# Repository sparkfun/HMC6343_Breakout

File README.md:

SparkFun HMC6343 Breakout
=========================

[*SparkFun HMC6343 Breakout (SEN-12916)*](https://www.sparkfun.com/products/12916)

A Breakout Board for the high end HMC6343 magnetometer.
The HMC6343 is a fully integrated high end electronic compass module that can compute and give you a heading direction that’s accurate within a couple degrees.

Repository Contents
-------------------
* **/Hardware** - All Eagle design files (.brd, .sch)
* **/Production** - Test bed files and production panel files

Documentation
--------------
* **[Library](https://github.com/sparkfun/SparkFun_HMC6343_Arduino_Library)** - Arduino library for the HMC6343.
* **[Hookup Guide](https://learn.sparkfun.com/tutorials/hmc6343-3-axis-compass-hookup-guide)** - Basic hookup guide for the HMC6343.
* **[SparkFun Fritzing repo](https://github.com/sparkfun/Fritzing_Parts)** - Fritzing diagrams for SparkFun products.
* **[SparkFun 3D Model repo](https://github.com/sparkfun/3D_Models)** - 3D models of SparkFun products. 
* **[SparkFun Graphical Datasheets](https://github.com/sparkfun/Graphical_Datasheets)** -Graphical Datasheets for various SparkFun products.

Version History
---------------

* [v_H1.0_L1.1.0](https://github.com/sparkfun/HMC6343_Breakout/tree/v_H1.0_L1.1.0) - Hardware version 1.0, library version 1.1.0. Compatible with Arduino 1.6+ 
* [vH10F10](https://github.com/sparkfun/HMC6343_Breakout/tree/vH10F10) - Hardware version 1.0, firmware version 1.0

License Information
-------------------

This product is _**open source**_! 

Please review the LICENSE.md file for license information. 

If you have any questions or concerns on licensing, please contact technical support on our [SparkFun forums](https://forum.sparkfun.com/viewforum.php?f=152).

Distributed as-is; no warranty is given.

- Your friends at SparkFun.

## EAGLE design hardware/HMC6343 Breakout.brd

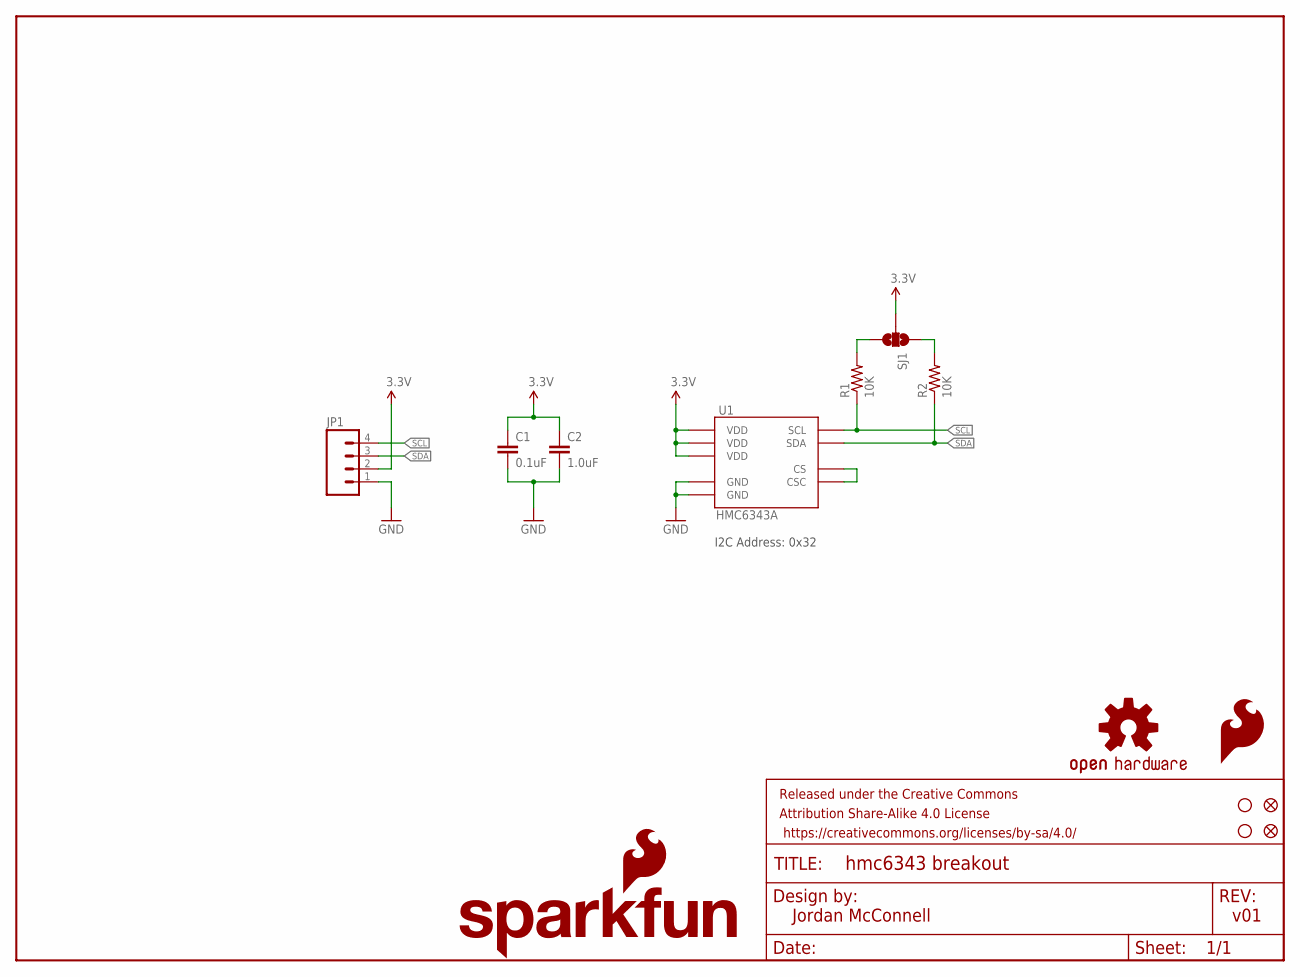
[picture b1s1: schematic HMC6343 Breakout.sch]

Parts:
C1: 0.1uF; 0603-CAP
C2: 1.0uF; 0603-CAP
FID1, FID2: FIDUCIAL1X2; FIDUCIAL-1X2
FRAME1: FRAME-LETTER; CREATIVE_COMMONS
JP1: M04PTH; 1X04
LOGO1: SFE_LOGO_FLAME.1_INCH; SFE_LOGO_FLAME_.1
LOGO2: SFE_LOGO_NAME_FLAME.1_INCH; SFE_LOGO_NAME_FLAME_.1
LOGO3: OSHW-LOGOS; OSHW-LOGO-S
R1, R2: 10K; 0603-RES
SJ1: SOLDERJUMPER_2WAYPASTE1&2&3; SJ_3_PASTE1&2&3
STANDOFF1, STANDOFF2: STAND-OFF
U1: HMC6343A; LCC36

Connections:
3.3V: C1.1, C2.1, JP1.2, SJ1.2, U1.3 (VDD), U1.11 (VDD), U1.21 (VDD)
GND: C1.2, C2.2, JP1.1, U1.25 (GND), U1.29 (GND)
unnamed: U1.22 (CS), U1.35 (CSC)
unnamed: R1.2, SJ1.3
unnamed: R2.2, SJ1.1
SCL: JP1.4, R1.1, U1.32 (SCL)
SDA: JP1.3, R2.1, U1.36 (SDA)

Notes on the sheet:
Jordan McConnell
v01
I2C Address: 0x32

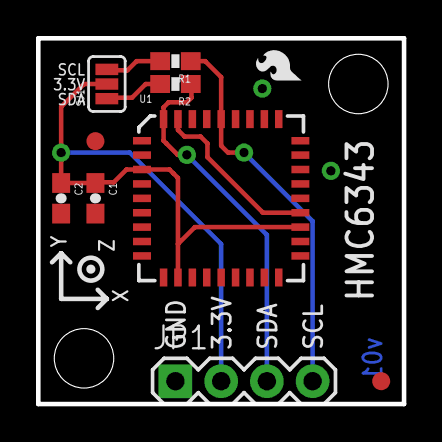
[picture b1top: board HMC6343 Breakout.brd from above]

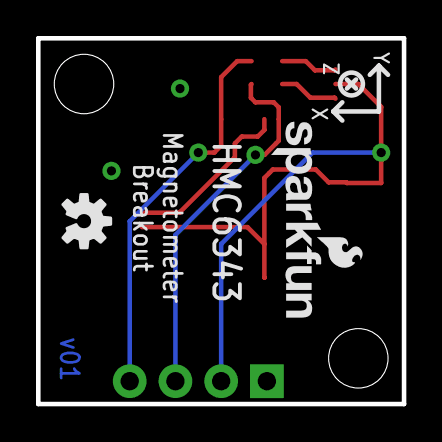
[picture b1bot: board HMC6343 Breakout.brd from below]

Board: 2 copper layers, 20.3 x 20.3 mm, 15 parts (2 on the bottom side), 7 nets.

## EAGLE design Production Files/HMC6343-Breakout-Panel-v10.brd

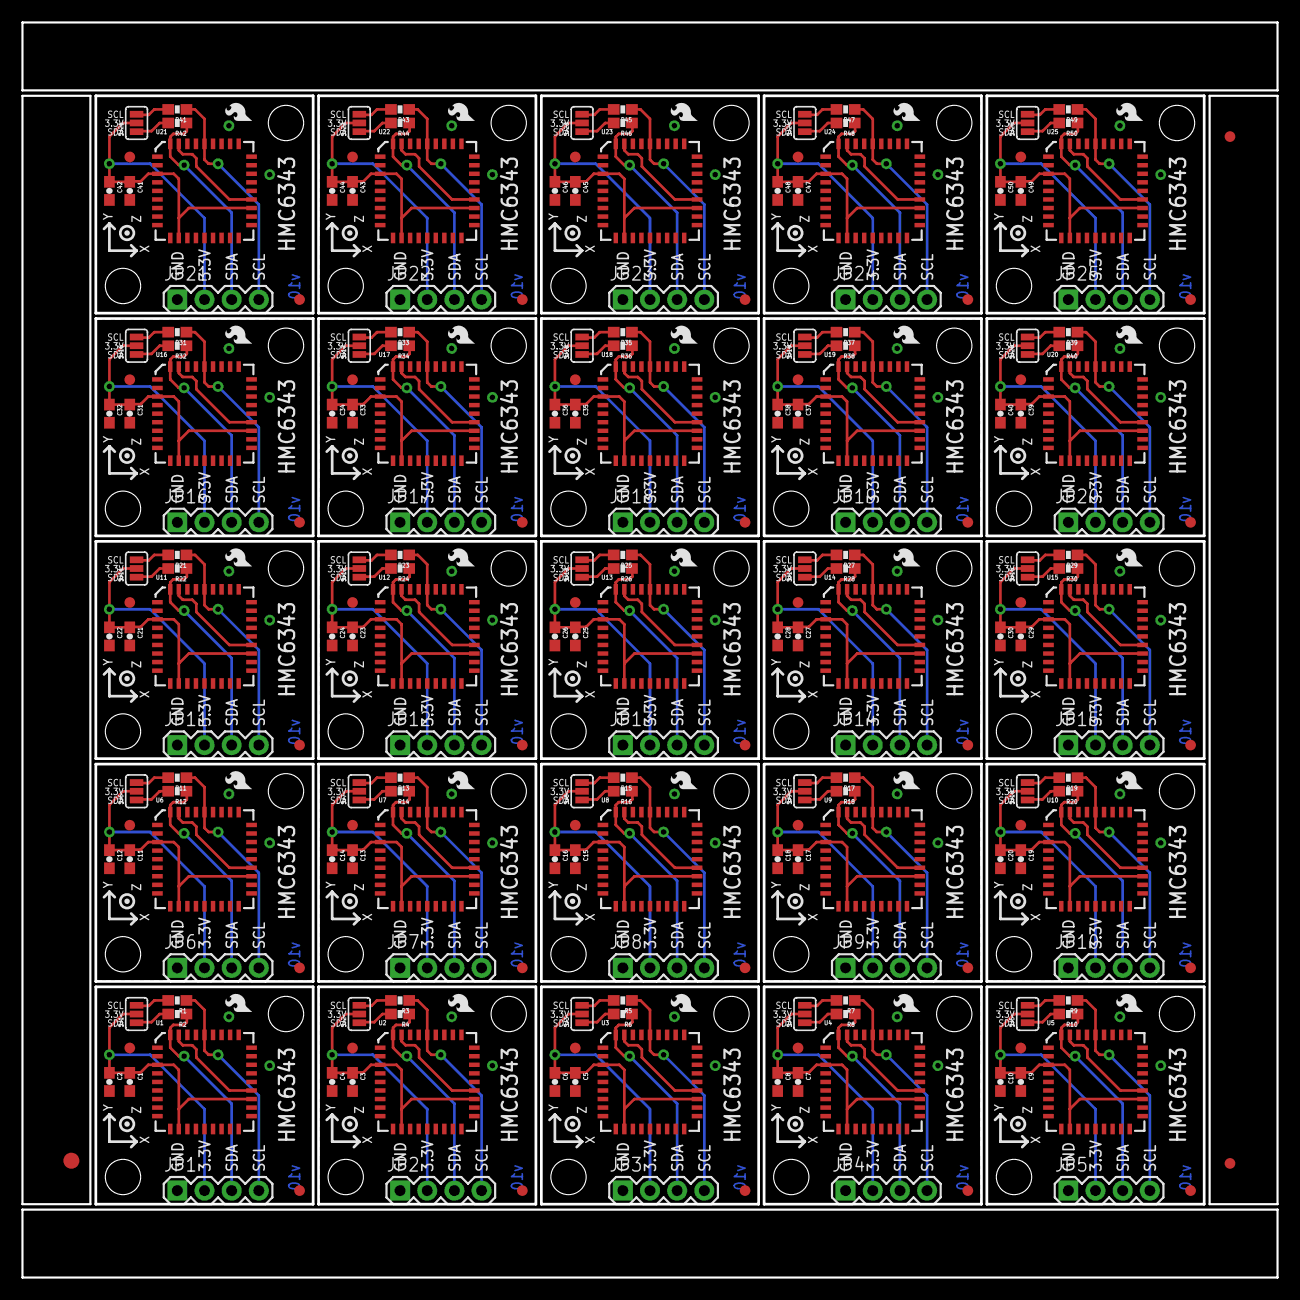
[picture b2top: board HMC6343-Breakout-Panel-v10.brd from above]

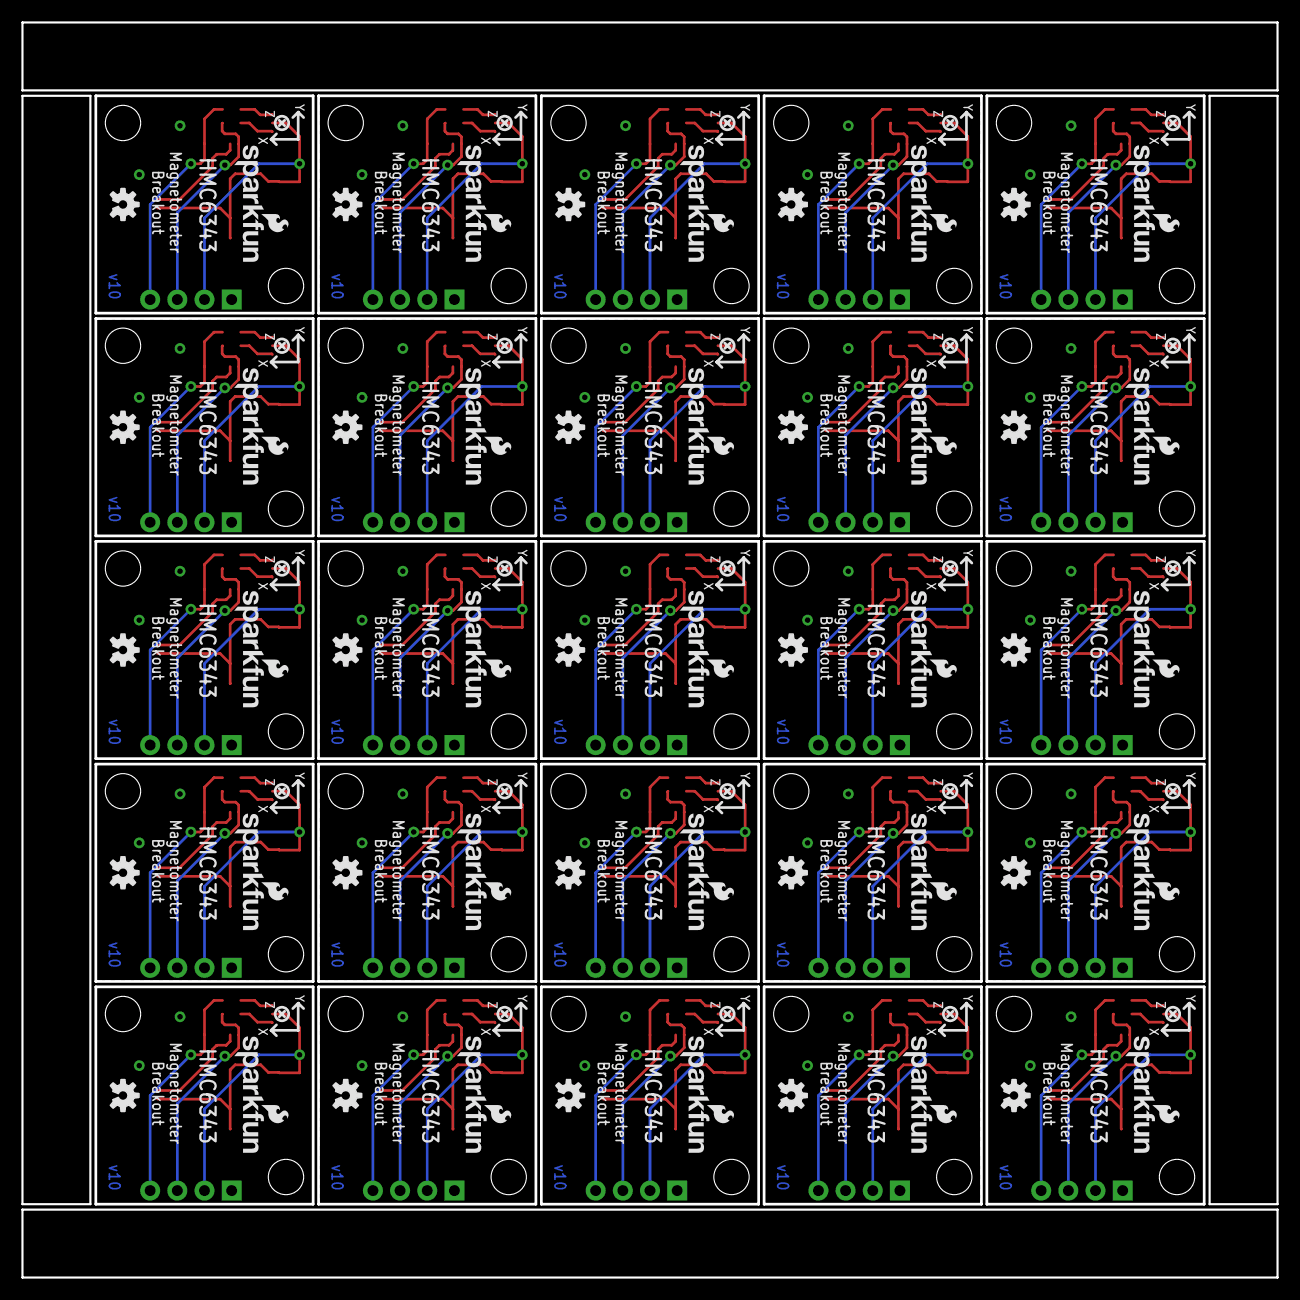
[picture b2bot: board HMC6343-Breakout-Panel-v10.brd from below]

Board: 2 copper layers, 117.3 x 117.3 mm, 353 parts (50 on the bottom side), 175 nets.

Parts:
C1, C3, C5, C7, C9, C11, C13, C15, C17, C19, C21, C23, C25, C27, C29, C31, C33, C35, C37, C39, C41, C43, C45, C47, C49: 0.1uF; 0603-CAP
C2, C4, C6, C8, C10, C12, C14, C16, C18, C20, C22, C24, C26, C28, C30, C32, C34, C36, C38, C40, C42, C44, C46, C48, C50: 1.0uF; 0603-CAP
E$1: FIDUCIAL-1.5X3
E$4, E$6: FIDUCIAL-1X2
FID1, FID2, FID3, FID4, FID5, FID6, FID7, FID8, FID9, FID10, FID11, FID12, FID13, FID14, FID15, FID16, FID17, FID18, FID19, FID20, FID21, FID22, FID23, FID24, FID25, FID26, FID27, FID28, FID29, FID30, FID31, FID32, FID33, FID34, FID35, FID36, FID37, FID38, FID39, FID40, FID41, FID42, FID43, FID44, FID45, FID46, FID47, FID48, FID49, FID50: FIDUCIAL1X2; FIDUCIAL-1X2
JP1, JP2, JP3, JP4, JP5, JP6, JP7, JP8, JP9, JP10, JP11, JP12, JP13, JP14, JP15, JP16, JP17, JP18, JP19, JP20, JP21, JP22, JP23, JP24, JP25: 1X04
LOGO1, LOGO4, LOGO7, LOGO10, LOGO13, LOGO16, LOGO19, LOGO22, LOGO25, LOGO28, LOGO31, LOGO34, LOGO37, LOGO40, LOGO43, LOGO46, LOGO49, LOGO52, LOGO55, LOGO58, LOGO61, LOGO64, LOGO67, LOGO70, LOGO73: SFE_LOGO_FLAME.1_INCH; SFE_LOGO_FLAME_.1
LOGO2, LOGO5, LOGO8, LOGO11, LOGO14, LOGO17, LOGO20, LOGO23, LOGO26, LOGO29, LOGO32, LOGO35, LOGO38, LOGO41, LOGO44, LOGO47, LOGO50, LOGO53, LOGO56, LOGO59, LOGO62, LOGO65, LOGO68, LOGO71, LOGO74: SFE_LOGO_NAME_FLAME.1_INCH; SFE_LOGO_NAME_FLAME_.1
LOGO3, LOGO6, LOGO9, LOGO12, LOGO15, LOGO18, LOGO21, LOGO24, LOGO27, LOGO30, LOGO33, LOGO36, LOGO39, LOGO42, LOGO45, LOGO48, LOGO51, LOGO54, LOGO57, LOGO60, LOGO63, LOGO66, LOGO69, LOGO72, LOGO75: OSHW-LOGOS; OSHW-LOGO-S
R1, R2, R3, R4, R5, R6, R7, R8, R9, R10, R11, R12, R13, R14, R15, R16, R17, R18, R19, R20, R21, R22, R23, R24, R25, R26, R27, R28, R29, R30, R31, R32, R33, R34, R35, R36, R37, R38, R39, R40, R41, R42, R43, R44, R45, R46, R47, R48, R49, R50: 10K; 0603-RES
SJ1, SJ2, SJ3, SJ4, SJ5, SJ6, SJ7, SJ8, SJ9, SJ10, SJ11, SJ12, SJ13, SJ14, SJ15, SJ16, SJ17, SJ18, SJ19, SJ20, SJ21, SJ22, SJ23, SJ24, SJ25: SJ_3_PASTE1&2&3
STANDOFF1, STANDOFF2, STANDOFF3, STANDOFF4, STANDOFF5, STANDOFF6, STANDOFF7, STANDOFF8, STANDOFF9, STANDOFF10, STANDOFF11, STANDOFF12, STANDOFF13, STANDOFF14, STANDOFF15, STANDOFF16, STANDOFF17, STANDOFF18, STANDOFF19, STANDOFF20, STANDOFF21, STANDOFF22, STANDOFF23, STANDOFF24, STANDOFF25, STANDOFF26, STANDOFF27, STANDOFF28, STANDOFF29, STANDOFF30, STANDOFF31, STANDOFF32, STANDOFF33, STANDOFF34, STANDOFF35, STANDOFF36, STANDOFF37, STANDOFF38, STANDOFF39, STANDOFF40, STANDOFF41, STANDOFF42, STANDOFF43, STANDOFF44, STANDOFF45, STANDOFF46, STANDOFF47, STANDOFF48, STANDOFF49, STANDOFF50: STAND-OFF
U1, U2, U3, U4, U5, U6, U7, U8, U9, U10, U11, U12, U13, U14, U15, U16, U17, U18, U19, U20, U21, U22, U23, U24, U25: HMC6343A; LCC36

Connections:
3.3V: C1.1, C2.1, JP1.2, SJ1.2, U1.3, U1.11, U1.21
3.3V1: C3.1, C4.1, JP2.2, SJ2.2, U2.3, U2.11, U2.21
3.3V2: C5.1, C6.1, JP3.2, SJ3.2, U3.3, U3.11, U3.21
3.3V3: C7.1, C8.1, JP4.2, SJ4.2, U4.3, U4.11, U4.21
3.3V4: C9.1, C10.1, JP5.2, SJ5.2, U5.3, U5.11, U5.21
3.3V5: C11.1, C12.1, JP6.2, SJ6.2, U6.3, U6.11, U6.21
3.3V6: C13.1, C14.1, JP7.2, SJ7.2, U7.3, U7.11, U7.21
3.3V7: C15.1, C16.1, JP8.2, SJ8.2, U8.3, U8.11, U8.21
3.3V8: C17.1, C18.1, JP9.2, SJ9.2, U9.3, U9.11, U9.21
3.3V9: C19.1, C20.1, JP10.2, SJ10.2, U10.3, U10.11, U10.21
3.3V10: C21.1, C22.1, JP11.2, SJ11.2, U11.3, U11.11, U11.21
3.3V11: C23.1, C24.1, JP12.2, SJ12.2, U12.3, U12.11, U12.21
3.3V12: C25.1, C26.1, JP13.2, SJ13.2, U13.3, U13.11, U13.21
3.3V13: C27.1, C28.1, JP14.2, SJ14.2, U14.3, U14.11, U14.21
3.3V14: C29.1, C30.1, JP15.2, SJ15.2, U15.3, U15.11, U15.21
3.3V15: C31.1, C32.1, JP16.2, SJ16.2, U16.3, U16.11, U16.21
3.3V16: C33.1, C34.1, JP17.2, SJ17.2, U17.3, U17.11, U17.21
3.3V17: C35.1, C36.1, JP18.2, SJ18.2, U18.3, U18.11, U18.21
3.3V18: C37.1, C38.1, JP19.2, SJ19.2, U19.3, U19.11, U19.21
3.3V19: C39.1, C40.1, JP20.2, SJ20.2, U20.3, U20.11, U20.21
3.3V20: C41.1, C42.1, JP21.2, SJ21.2, U21.3, U21.11, U21.21
3.3V21: C43.1, C44.1, JP22.2, SJ22.2, U22.3, U22.11, U22.21
3.3V22: C45.1, C46.1, JP23.2, SJ23.2, U23.3, U23.11, U23.21
3.3V23: C47.1, C48.1, JP24.2, SJ24.2, U24.3, U24.11, U24.21
3.3V24: C49.1, C50.1, JP25.2, SJ25.2, U25.3, U25.11, U25.21
GND: C1.2, C2.2, JP1.1, U1.25, U1.29
GND1: C3.2, C4.2, JP2.1, U2.25, U2.29
GND2: C5.2, C6.2, JP3.1, U3.25, U3.29
GND3: C7.2, C8.2, JP4.1, U4.25, U4.29
GND4: C9.2, C10.2, JP5.1, U5.25, U5.29
GND5: C11.2, C12.2, JP6.1, U6.25, U6.29
GND6: C13.2, C14.2, JP7.1, U7.25, U7.29
GND7: C15.2, C16.2, JP8.1, U8.25, U8.29
GND8: C17.2, C18.2, JP9.1, U9.25, U9.29
GND9: C19.2, C20.2, JP10.1, U10.25, U10.29
GND10: C21.2, C22.2, JP11.1, U11.25, U11.29
GND11: C23.2, C24.2, JP12.1, U12.25, U12.29
GND12: C25.2, C26.2, JP13.1, U13.25, U13.29
GND13: C27.2, C28.2, JP14.1, U14.25, U14.29
GND14: C29.2, C30.2, JP15.1, U15.25, U15.29
GND15: C31.2, C32.2, JP16.1, U16.25, U16.29
GND16: C33.2, C34.2, JP17.1, U17.25, U17.29
GND17: C35.2, C36.2, JP18.1, U18.25, U18.29
GND18: C37.2, C38.2, JP19.1, U19.25, U19.29
GND19: C39.2, C40.2, JP20.1, U20.25, U20.29
GND20: C41.2, C42.2, JP21.1, U21.25, U21.29
GND21: C43.2, C44.2, JP22.1, U22.25, U22.29
GND22: C45.2, C46.2, JP23.1, U23.25, U23.29
GND23: C47.2, C48.2, JP24.1, U24.25, U24.29
GND24: C49.2, C50.2, JP25.1, U25.25, U25.29
unnamed: U1.22, U1.35
unnamed: U2.22, U2.35
unnamed: R3.2, SJ2.3
unnamed: R1.2, SJ1.3
unnamed: R2.2, SJ1.1
unnamed: R4.2, SJ2.1
unnamed: U3.22, U3.35
unnamed: R5.2, SJ3.3
unnamed: R6.2, SJ3.1
unnamed: U4.22, U4.35
unnamed: R7.2, SJ4.3
unnamed: R8.2, SJ4.1
unnamed: U5.22, U5.35
unnamed: R9.2, SJ5.3
unnamed: R10.2, SJ5.1
unnamed: U6.22, U6.35
unnamed: R11.2, SJ6.3
unnamed: R12.2, SJ6.1
unnamed: U7.22, U7.35
unnamed: R13.2, SJ7.3
unnamed: R14.2, SJ7.1
unnamed: U8.22, U8.35
unnamed: R15.2, SJ8.3
unnamed: R16.2, SJ8.1
unnamed: U9.22, U9.35
unnamed: R17.2, SJ9.3
unnamed: R18.2, SJ9.1
unnamed: U10.22, U10.35
unnamed: R19.2, SJ10.3
unnamed: R20.2, SJ10.1
unnamed: U11.22, U11.35
unnamed: R21.2, SJ11.3
unnamed: R22.2, SJ11.1
unnamed: U12.22, U12.35
unnamed: R23.2, SJ12.3
unnamed: R24.2, SJ12.1
unnamed: U13.22, U13.35
unnamed: R25.2, SJ13.3
unnamed: R26.2, SJ13.1
unnamed: U14.22, U14.35
unnamed: R27.2, SJ14.3
unnamed: R28.2, SJ14.1
unnamed: U15.22, U15.35
unnamed: R29.2, SJ15.3
unnamed: R30.2, SJ15.1
unnamed: U16.22, U16.35
unnamed: R31.2, SJ16.3
unnamed: R32.2, SJ16.1
unnamed: U17.22, U17.35
unnamed: R33.2, SJ17.3
unnamed: R34.2, SJ17.1
unnamed: U18.22, U18.35
unnamed: R35.2, SJ18.3
unnamed: R36.2, SJ18.1
unnamed: U19.22, U19.35
unnamed: R37.2, SJ19.3
unnamed: R38.2, SJ19.1
unnamed: U20.22, U20.35
unnamed: R39.2, SJ20.3
unnamed: R40.2, SJ20.1
unnamed: U21.22, U21.35
unnamed: R41.2, SJ21.3
unnamed: R42.2, SJ21.1
unnamed: U22.22, U22.35
unnamed: R43.2, SJ22.3
unnamed: R44.2, SJ22.1
unnamed: U23.22, U23.35
unnamed: R45.2, SJ23.3
unnamed: R46.2, SJ23.1
unnamed: U24.22, U24.35
unnamed: R47.2, SJ24.3
unnamed: R48.2, SJ24.1
unnamed: U25.22, U25.35
unnamed: R49.2, SJ25.3
unnamed: R50.2, SJ25.1
SCL: JP1.4, R1.1, U1.32
SCL1: JP2.4, R3.1, U2.32
SCL2: JP3.4, R5.1, U3.32
SCL3: JP4.4, R7.1, U4.32
SCL4: JP5.4, R9.1, U5.32
SCL5: JP6.4, R11.1, U6.32
SCL6: JP7.4, R13.1, U7.32
SCL7: JP8.4, R15.1, U8.32
SCL8: JP9.4, R17.1, U9.32
SCL9: JP10.4, R19.1, U10.32
SCL10: JP11.4, R21.1, U11.32
SCL11: JP12.4, R23.1, U12.32
SCL12: JP13.4, R25.1, U13.32
SCL13: JP14.4, R27.1, U14.32
SCL14: JP15.4, R29.1, U15.32
SCL15: JP16.4, R31.1, U16.32
SCL16: JP17.4, R33.1, U17.32
SCL17: JP18.4, R35.1, U18.32
SCL18: JP19.4, R37.1, U19.32
SCL19: JP20.4, R39.1, U20.32
SCL20: JP21.4, R41.1, U21.32
SCL21: JP22.4, R43.1, U22.32
SCL22: JP23.4, R45.1, U23.32
SCL23: JP24.4, R47.1, U24.32
SCL24: JP25.4, R49.1, U25.32
SDA: JP1.3, R2.1, U1.36
SDA1: JP2.3, R4.1, U2.36
SDA2: JP3.3, R6.1, U3.36
SDA3: JP4.3, R8.1, U4.36
SDA4: JP5.3, R10.1, U5.36
SDA5: JP6.3, R12.1, U6.36
SDA6: JP7.3, R14.1, U7.36
SDA7: JP8.3, R16.1, U8.36
SDA8: JP9.3, R18.1, U9.36
SDA9: JP10.3, R20.1, U10.36
SDA10: JP11.3, R22.1, U11.36
SDA11: JP12.3, R24.1, U12.36
SDA12: JP13.3, R26.1, U13.36
SDA13: JP14.3, R28.1, U14.36
SDA14: JP15.3, R30.1, U15.36
SDA15: JP16.3, R32.1, U16.36
SDA16: JP17.3, R34.1, U17.36
SDA17: JP18.3, R36.1, U18.36
SDA18: JP19.3, R38.1, U19.36
SDA19: JP20.3, R40.1, U20.36
SDA20: JP21.3, R42.1, U21.36
SDA21: JP22.3, R44.1, U22.36
SDA22: JP23.3, R46.1, U23.36
SDA23: JP24.3, R48.1, U24.36
SDA24: JP25.3, R50.1, U25.36

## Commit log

2014-05-01 v01 ready for review
2014-05-05 v01 updated based on review feedback
2014-06-30 v10, ready for reds
2014-07-01 created panel v10
2014-07-18 Added Arduino library with 2 example sketches
2014-07-31 updated readme for release
2016-02-17 Updating to new directory structure, fixing README links
2016-02-17 Squashed 'Libraries/Arduino/' content from commit 5347ae9
    git-subtree-dir: Libraries/Arduino
    git-subtree-split: 5347ae99e652ef31a632faf9027846f147231587
2016-02-17 Updating README description of part
2016-02-17 Fixing typos in README
2016-02-17 Fixing typo
2020-05-28 Remove Redundancy
    Removing library from the hardware repo so that latest changes and issues are filed with the Arduino Library repo.
2020-05-28 Adjusting Hardware Path

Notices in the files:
parts and their libraries:
SparkFun-Aesthetics: Licensing: Creative Commons ShareAlike 4.0 International - https://creativecommons.org/licenses/by-sa/4.0
SparkFun-Aesthetics: Released under the Creative Commons Attribution Share-Alike 4.0 License
SparkFun-Aesthetics: https://creativecommons.org/licenses/by-sa/4.0
